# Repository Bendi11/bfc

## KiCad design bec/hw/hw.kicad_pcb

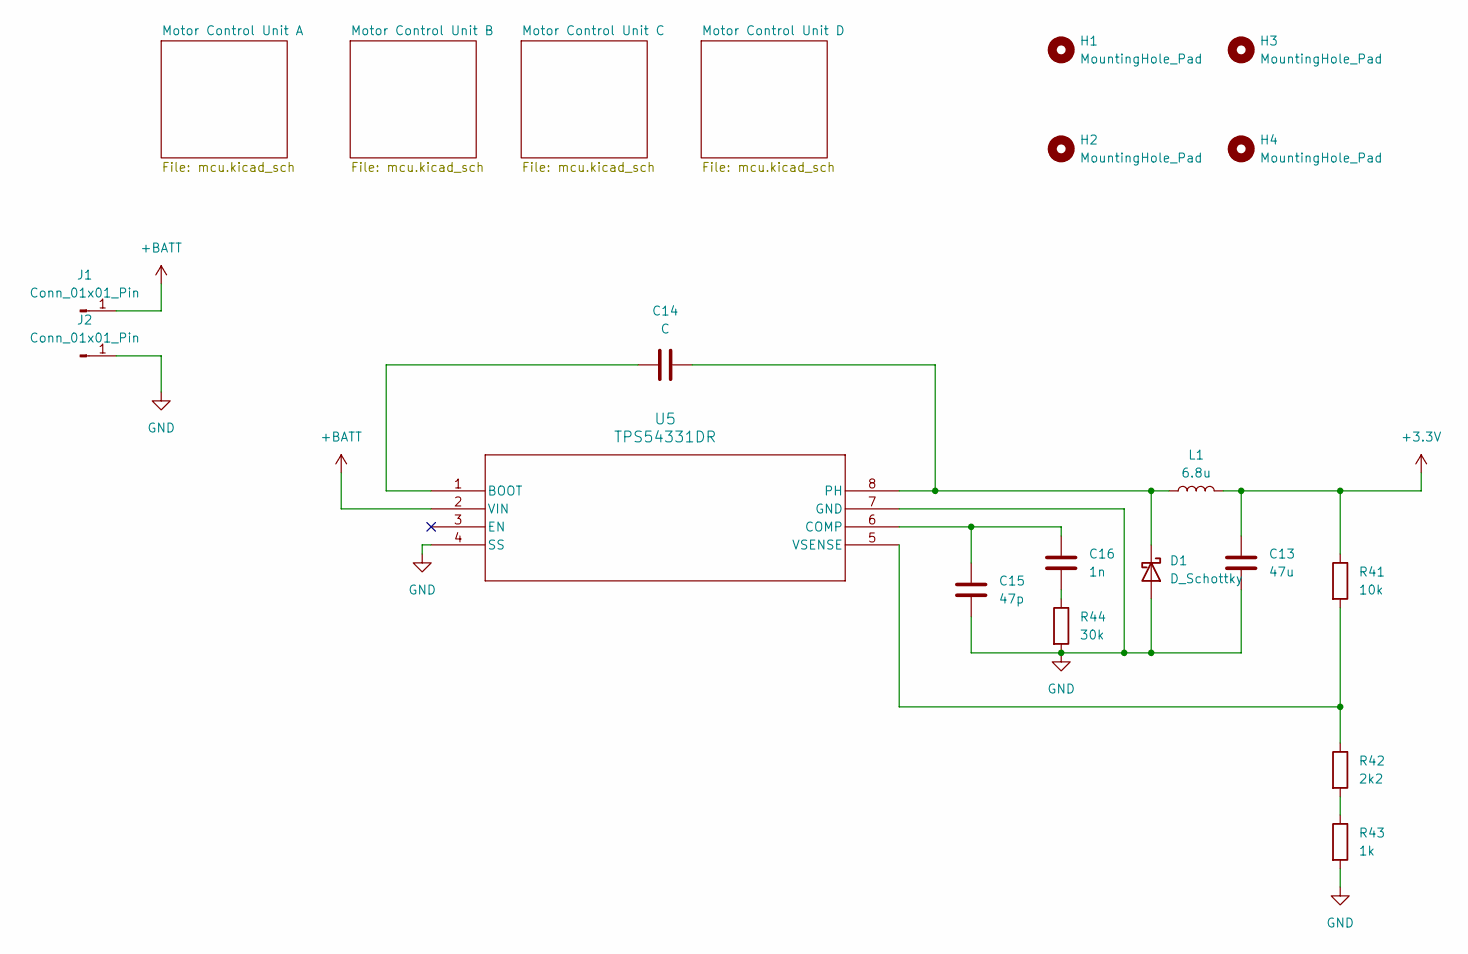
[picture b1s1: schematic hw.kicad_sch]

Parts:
C13: 47u; C_0805_2012Metric
C14: C; C_0805_2012Metric
C15: 47p; C_0805_2012Metric
C16: 1n; C_0805_2012Metric
D1: D_Schottky
H1, H2, H3, H4: MountingHole_Pad; MountingHole_4.3mm_M4_DIN965
J1, J2: Conn_01x01_Pin; SolderWirePad_1x01_SMD_5x10mm
L1: 6.8u
R41: 10k; R_0805_2012Metric
R42: 2k2; R_0805_2012Metric
R43: 1k; R_0805_2012Metric
R44: 30k; R_0805_2012Metric
U5: TPS54331DR; D8

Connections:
+3.3V: C13.1, L1.2, R41.1; also elsewhere on the board
+BATT: J1.1, U5.2 (VIN); also elsewhere on the board
GND: C13.2, C15.1, D1.2 (A), J2.1, R43.2, R44.2, U5.4 (SS), U5.7 (GND); also elsewhere on the board
unnamed: C16.1, R44.1
unnamed: C14.2, D1.1 (K), L1.1, U5.8 (PH)
unnamed: R42.2, R43.1
unnamed: C14.1, U5.1 (BOOT)
unnamed: C15.2, C16.2, U5.6 (COMP)
unnamed: R41.2, R42.1, U5.5 (VSENSE)

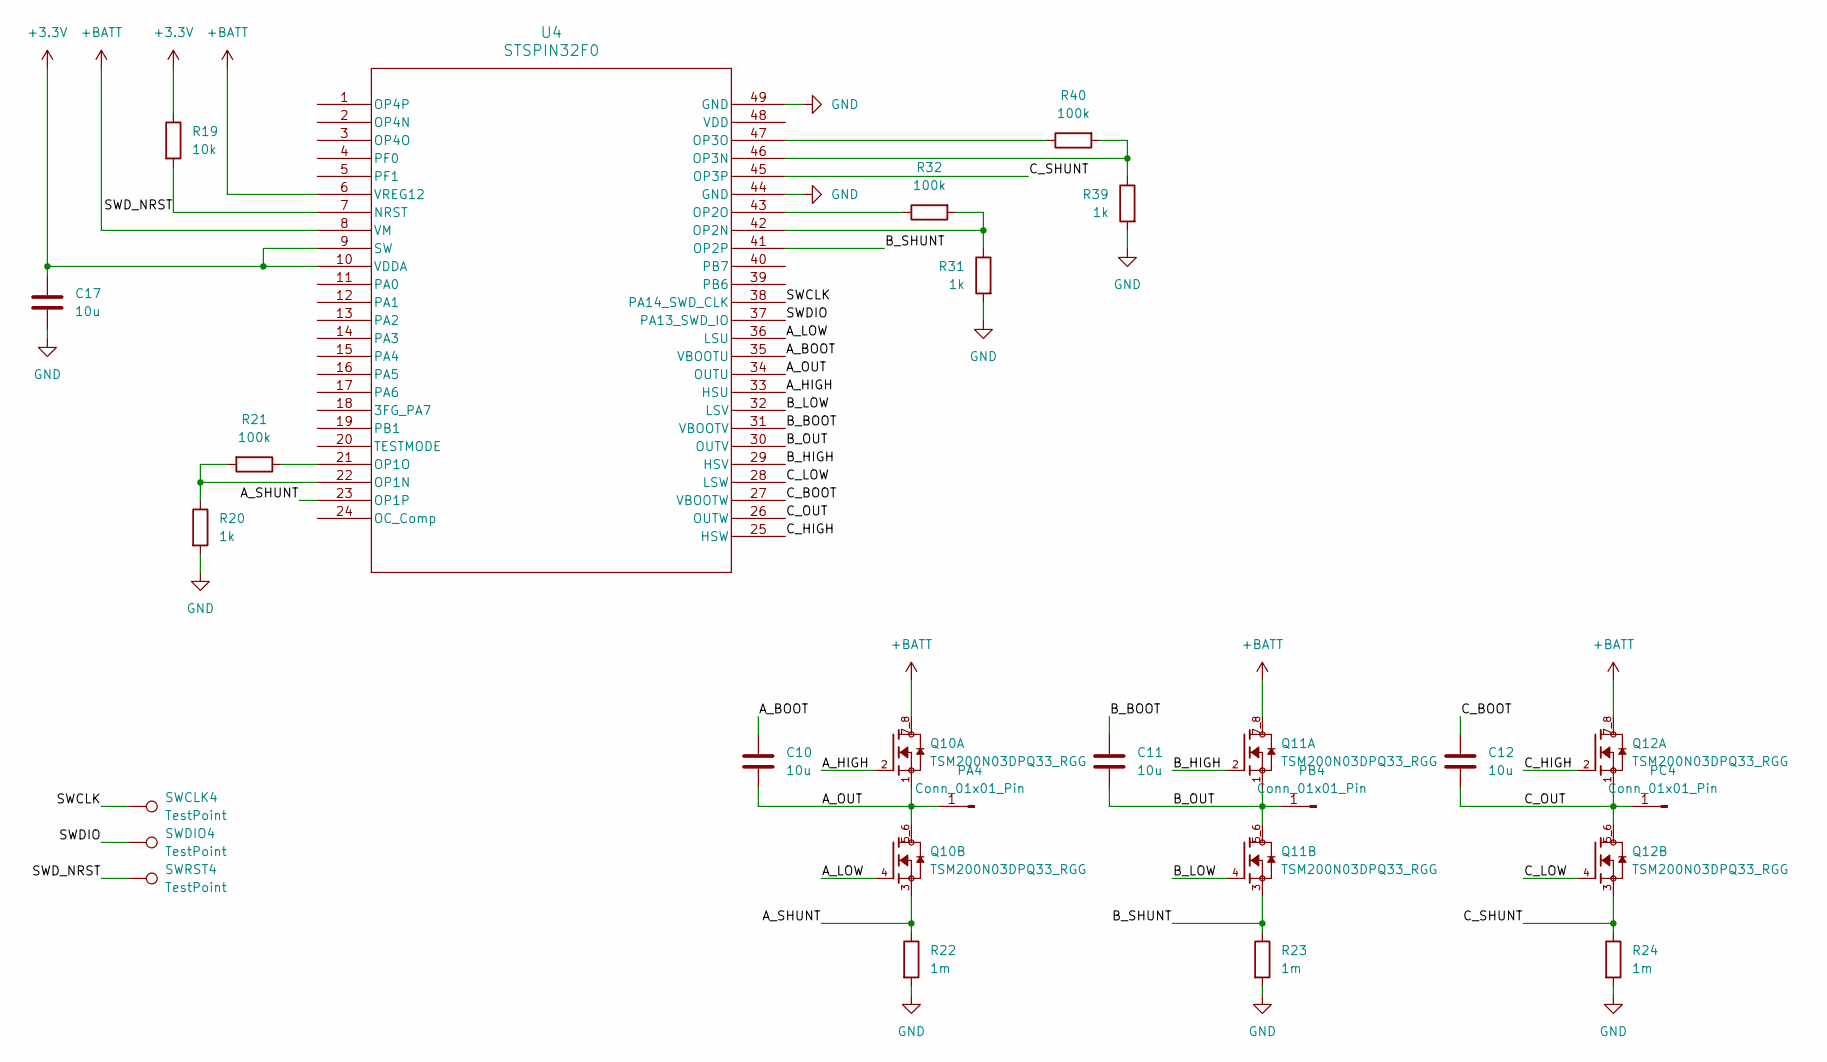
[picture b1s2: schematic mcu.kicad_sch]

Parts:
C10, C11, C12, C17: 10u; C_0805_2012Metric
PA4: Conn_01x01_Pin
PB4: Conn_01x01_Pin
PC4: Conn_01x01_Pin
Q10, Q11, Q12: TSM200N03DPQ33_RGG; TSM200N03DPQ33_RGG_TRANS_TSM200N03DPQ33_RGG; PARTREV B1710
R19: 10k; R_0805_2012Metric
R20, R31, R39: 1k; R_0805_2012Metric
R21, R32, R40: 100k; R_0805_2012Metric
R22, R23, R24: 1m; R_1210_3225Metric
SWCLK4: TestPoint; TestPoint_Pad_D1.0mm
SWDIO4: TestPoint; TestPoint_Pad_D1.0mm
SWRST4: TestPoint; TestPoint_Pad_D1.0mm
U4: STSPIN32F0; VFQFPN48_7X7X1_STM

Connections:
+3.3V: C17.1, R19.1, U4.9 (SW), U4.10 (VDDA); also elsewhere on the board
+BATT: Q10.7_8, Q11.7_8, Q12.7_8, U4.6 (VREG12), U4.8 (VM); also elsewhere on the board
/Motor Control Unit D/A_BOOT: C10.1, U4.35 (VBOOTU)
/Motor Control Unit D/A_HIGH: Q10.2, U4.33 (HSU)
/Motor Control Unit D/A_LOW: Q10.4, U4.36 (LSU)
/Motor Control Unit D/A_OUT: C10.2, Q10.1, Q10.5_6, U4.34 (OUTU)
/Motor Control Unit D/A_SHUNT: Q10.3, R22.1, U4.23 (OP1P)
/Motor Control Unit D/B_BOOT: C11.1, U4.31 (VBOOTV)
/Motor Control Unit D/B_HIGH: Q11.2, U4.29 (HSV)
/Motor Control Unit D/B_LOW: Q11.4, U4.32 (LSV)
/Motor Control Unit D/B_OUT: C11.2, Q11.1, Q11.5_6, U4.30 (OUTV)
/Motor Control Unit D/B_SHUNT: Q11.3, R23.1, U4.41 (OP2P)
/Motor Control Unit D/C_BOOT: C12.1, U4.27 (VBOOTW)
/Motor Control Unit D/C_HIGH: Q12.2, U4.25 (HSW)
/Motor Control Unit D/C_LOW: Q12.4, U4.28 (LSW)
/Motor Control Unit D/C_OUT: C12.2, Q12.1, Q12.5_6, U4.26 (OUTW)
/Motor Control Unit D/C_SHUNT: Q12.3, R24.1, U4.45 (OP3P)
/Motor Control Unit D/SWCLK: SWCLK4.1, U4.38 (PA14_SWD_CLK)
/Motor Control Unit D/SWDIO: SWDIO4.1, U4.37 (PA13_SWD_IO)
/Motor Control Unit D/SWD_NRST: R19.2, SWRST4.1, U4.7 (NRST)
GND: C17.2, R20.2, R22.2, R23.2, R24.2, R31.2, R39.2, U4.44 (GND), U4.49 (GND); also elsewhere on the board
unnamed: R20.1, R21.2, U4.22 (OP1N)
unnamed: R21.1, U4.21 (OP1O)
unnamed: R31.1, R32.2, U4.42 (OP2N)
unnamed: R32.1, U4.43 (OP2O)
unnamed: R39.1, R40.2, U4.46 (OP3N)
unnamed: R40.1, U4.47 (OP3O)

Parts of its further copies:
C1, C2, C3, C4, C5, C6, C7, C8, C9, C18, C19, C20: 10u; C_0805_2012Metric
Q1, Q2, Q3, Q4, Q5, Q6, Q7, Q8, Q9: TSM200N03DPQ33_RGG; TSM200N03DPQ33_RGG_TRANS_TSM200N03DPQ33_RGG; PARTREV B1710
R1, R7, R13: 10k; R_0805_2012Metric
R2, R8, R14, R25, R27, R29, R33, R35, R37: 1k; R_0805_2012Metric
R3, R9, R15, R26, R28, R30, R34, R36, R38: 100k; R_0805_2012Metric
R4, R5, R6, R10, R11, R12, R16, R17, R18: 1m; R_1210_3225Metric
SWCLK1, SWCLK2, SWCLK3: TestPoint; TestPoint_Pad_D1.0mm
SWDIO1, SWDIO2, SWDIO3: TestPoint; TestPoint_Pad_D1.0mm
SWRST1, SWRST2, SWRST3: TestPoint; TestPoint_Pad_D1.0mm
U1, U2, U3: STSPIN32F0; VFQFPN48_7X7X1_STM

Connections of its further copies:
+3.3V: C18.1, C19.1, C20.1, R1.1, R7.1, R13.1, U1.9 (SW), U1.10 (VDDA), U2.9 (SW), U2.10 (VDDA), U3.9 (SW), U3.10 (VDDA); also elsewhere on the board
+BATT: Q1.7_8, Q2.7_8, Q3.7_8, Q4.7_8, Q5.7_8, Q6.7_8, Q7.7_8, Q8.7_8, Q9.7_8, U1.6 (VREG12), U1.8 (VM), U2.6 (VREG12), U2.8 (VM), U3.6 (VREG12), U3.8 (VM); also elsewhere on the board
/Motor Control Unit A/A_BOOT: C1.1, U1.35 (VBOOTU)
/Motor Control Unit A/A_HIGH: Q1.2, U1.33 (HSU)
/Motor Control Unit A/A_LOW: Q1.4, U1.36 (LSU)
/Motor Control Unit A/A_OUT: C1.2, Q1.1, Q1.5_6, U1.34 (OUTU)
/Motor Control Unit A/A_SHUNT: Q1.3, R4.1, U1.23 (OP1P)
/Motor Control Unit A/B_BOOT: C2.1, U1.31 (VBOOTV)
/Motor Control Unit A/B_HIGH: Q2.2, U1.29 (HSV)
/Motor Control Unit A/B_LOW: Q2.4, U1.32 (LSV)
/Motor Control Unit A/B_OUT: C2.2, Q2.1, Q2.5_6, U1.30 (OUTV)
/Motor Control Unit A/B_SHUNT: Q2.3, R5.1, U1.41 (OP2P)
/Motor Control Unit A/C_BOOT: C3.1, U1.27 (VBOOTW)
/Motor Control Unit A/C_HIGH: Q3.2, U1.25 (HSW)
/Motor Control Unit A/C_LOW: Q3.4, U1.28 (LSW)
/Motor Control Unit A/C_OUT: C3.2, Q3.1, Q3.5_6, U1.26 (OUTW)
/Motor Control Unit A/C_SHUNT: Q3.3, R6.1, U1.45 (OP3P)
/Motor Control Unit A/SWCLK: SWCLK1.1, U1.38 (PA14_SWD_CLK)
/Motor Control Unit A/SWDIO: SWDIO1.1, U1.37 (PA13_SWD_IO)
/Motor Control Unit A/SWD_NRST: R1.2, SWRST1.1, U1.7 (NRST)
/Motor Control Unit B/A_BOOT: C4.1, U2.35 (VBOOTU)
/Motor Control Unit B/A_HIGH: Q4.2, U2.33 (HSU)
/Motor Control Unit B/A_LOW: Q4.4, U2.36 (LSU)
/Motor Control Unit B/A_OUT: C4.2, Q4.1, Q4.5_6, U2.34 (OUTU)
/Motor Control Unit B/A_SHUNT: Q4.3, R10.1, U2.23 (OP1P)
/Motor Control Unit B/B_BOOT: C5.1, U2.31 (VBOOTV)
/Motor Control Unit B/B_HIGH: Q5.2, U2.29 (HSV)
/Motor Control Unit B/B_LOW: Q5.4, U2.32 (LSV)
/Motor Control Unit B/B_OUT: C5.2, Q5.1, Q5.5_6, U2.30 (OUTV)
/Motor Control Unit B/B_SHUNT: Q5.3, R11.1, U2.41 (OP2P)
/Motor Control Unit B/C_BOOT: C6.1, U2.27 (VBOOTW)
/Motor Control Unit B/C_HIGH: Q6.2, U2.25 (HSW)
/Motor Control Unit B/C_LOW: Q6.4, U2.28 (LSW)
/Motor Control Unit B/C_OUT: C6.2, Q6.1, Q6.5_6, U2.26 (OUTW)
/Motor Control Unit B/C_SHUNT: Q6.3, R12.1, U2.45 (OP3P)
/Motor Control Unit B/SWCLK: SWCLK2.1, U2.38 (PA14_SWD_CLK)
/Motor Control Unit B/SWDIO: SWDIO2.1, U2.37 (PA13_SWD_IO)
/Motor Control Unit B/SWD_NRST: R7.2, SWRST2.1, U2.7 (NRST)
/Motor Control Unit C/A_BOOT: C7.1, U3.35 (VBOOTU)
/Motor Control Unit C/A_HIGH: Q7.2, U3.33 (HSU)
/Motor Control Unit C/A_LOW: Q7.4, U3.36 (LSU)
/Motor Control Unit C/A_OUT: C7.2, Q7.1, Q7.5_6, U3.34 (OUTU)
/Motor Control Unit C/A_SHUNT: Q7.3, R16.1, U3.23 (OP1P)
/Motor Control Unit C/B_BOOT: C8.1, U3.31 (VBOOTV)
/Motor Control Unit C/B_HIGH: Q8.2, U3.29 (HSV)
/Motor Control Unit C/B_LOW: Q8.4, U3.32 (LSV)
/Motor Control Unit C/B_OUT: C8.2, Q8.1, Q8.5_6, U3.30 (OUTV)
/Motor Control Unit C/B_SHUNT: Q8.3, R17.1, U3.41 (OP2P)
/Motor Control Unit C/C_BOOT: C9.1, U3.27 (VBOOTW)
/Motor Control Unit C/C_HIGH: Q9.2, U3.25 (HSW)
/Motor Control Unit C/C_LOW: Q9.4, U3.28 (LSW)
/Motor Control Unit C/C_OUT: C9.2, Q9.1, Q9.5_6, U3.26 (OUTW)
/Motor Control Unit C/C_SHUNT: Q9.3, R18.1, U3.45 (OP3P)
/Motor Control Unit C/SWCLK: SWCLK3.1, U3.38 (PA14_SWD_CLK)
/Motor Control Unit C/SWDIO: SWDIO3.1, U3.37 (PA13_SWD_IO)
/Motor Control Unit C/SWD_NRST: R13.2, SWRST3.1, U3.7 (NRST)
GND: C18.2, C19.2, C20.2, R2.2, R4.2, R5.2, R6.2, R8.2, R10.2, R11.2, R12.2, R14.2, R16.2, R17.2, R18.2, R25.2, R27.2, R29.2, R33.2, R35.2, R37.2, U1.44 (GND), U1.49 (GND), U2.44 (GND), U2.49 (GND), U3.44 (GND), U3.49 (GND); also elsewhere on the board
unnamed: R2.1, R3.2, U1.22 (OP1N)
unnamed: R3.1, U1.21 (OP1O)
unnamed: R25.1, R26.2, U1.42 (OP2N)
unnamed: R26.1, U1.43 (OP2O)
unnamed: R33.1, R34.2, U1.46 (OP3N)
unnamed: R34.1, U1.47 (OP3O)
unnamed: R8.1, R9.2, U2.22 (OP1N)
unnamed: R9.1, U2.21 (OP1O)
unnamed: R27.1, R28.2, U2.42 (OP2N)
unnamed: R28.1, U2.43 (OP2O)
unnamed: R35.1, R36.2, U2.46 (OP3N)
unnamed: R36.1, U2.47 (OP3O)
unnamed: R14.1, R15.2, U3.22 (OP1N)
unnamed: R15.1, U3.21 (OP1O)
unnamed: R29.1, R30.2, U3.42 (OP2N)
unnamed: R30.1, U3.43 (OP2O)
unnamed: R37.1, R38.2, U3.46 (OP3N)
unnamed: R38.1, U3.47 (OP3O)

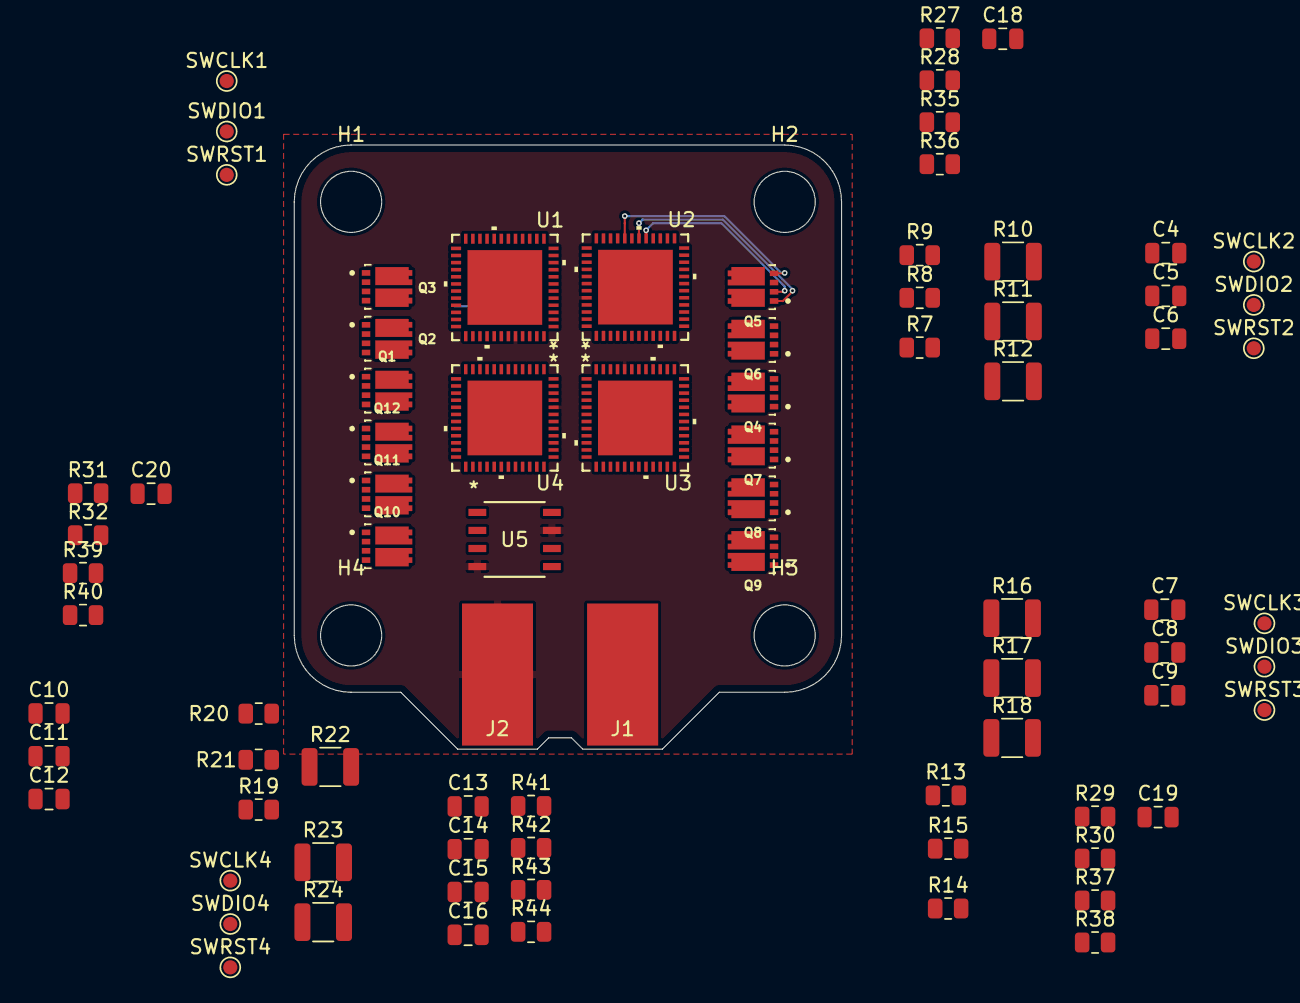
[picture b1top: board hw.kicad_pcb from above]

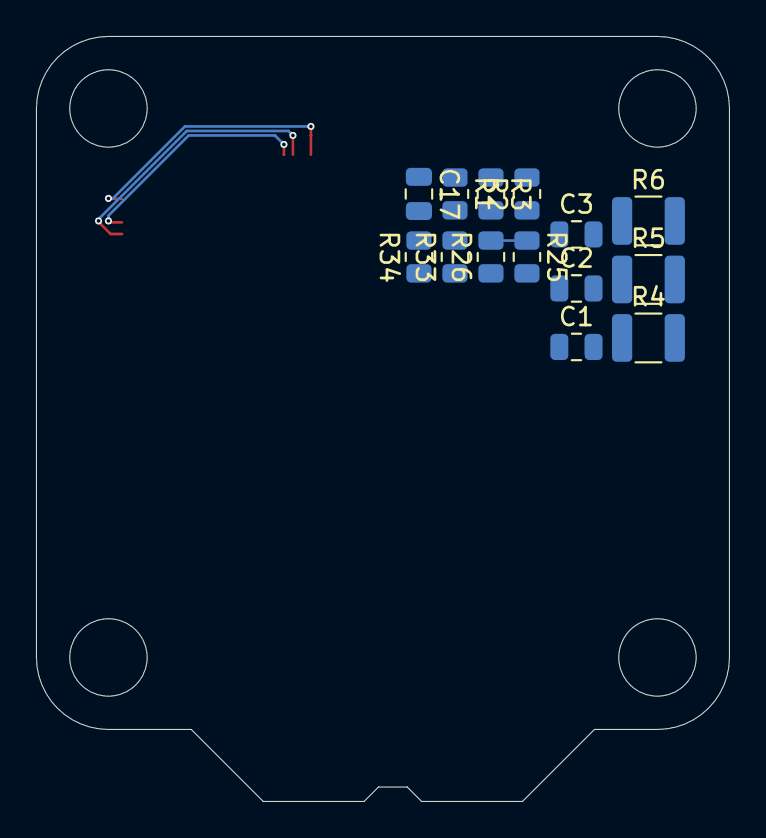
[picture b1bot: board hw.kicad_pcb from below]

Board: 2 copper layers, 38.5 x 42.5 mm, 99 parts (14 on the bottom side), 105 nets.

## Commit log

2024-12-19 Added STSPIN32F0 for ESC
2024-12-19 Started clarke-park transforms for ESC firmware
2024-12-20 Added motor phase half bridges
2024-12-22 Added TPS54331 for 3.3v supply
